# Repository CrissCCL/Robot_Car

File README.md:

# 🚗🤖 Assisted-Trajectory Robot Car

## 📖 Overview
This model robot car was developed and built to implement an assisted-trajectory (Drive by Wire) system. The system is controlled using a Teensy 4.0 microcontroller to enhance computational speed and stability.  

A gyroscope MPU6050 measures angular rate, while an H-bridge L298N drives the motors. The robot is operated via a Flysky FS-6X remote using a PPM/PWM modulated signal.

## 🧩 Hardware Notes — Pin Availability

The currently implemented PCB used in this robot car **does not expose Teensy 4.0 pins 12 and 13**, as the original board was designed for a specific application and limited I/O requirements.

As part of an ongoing hardware update, a **new pin expansion and routing strategy** is being developed.  
This updated PCB revision exposes **all relevant Teensy 4.0 pins**, including pins **12 and 13**, enabling greater flexibility and reuse across multiple projects.

This improvement aligns with the goal of creating **modular and reusable hardware blocks** that can be shared across multiple projects.

> 🔗 **NOTE:**  
> The updated pin expansion hardware is referenced in the **Related Repositories** section at the end of this document.

## 📂 Contents
- `/Hardware` → schematic, Gerbers.
- `/control_car` → C code for Teensy in the Arduino environment.
- `/control_car_bumpless_fix` → C code for Teensy in the Arduino environment, bumpless transfer bug fixed.

## 🌐 YouTube
📺 [My Playlist](https://youtube.com/playlist?list=PLy6JmHc8bVqIY5rbHkpyFbhlm4xQOCF1T&si=1QBgLZTLAjbxRnrU)

## ⚙️ System Description — Auto Robot (Assisted-Trajectory)
- **Controller:** Teensy 4.0 (high-speed MCU for improved stability and processing)  
- **Sensors:** Gyroscope (angular velocity) and supporting encoders/IMU as available  
- **Actuators:** Dual DC motors with H-bridge driver  
- **Control Strategy:** PI-assisted trajectory control (drive-by-wire)  
- **Sampling period:** **0.004 seconds (250 Hz)**  
- **Data transmission:** UART link to a **Raspberry Pi 4B** for logging and postprocessing  
- **Data logging:** Raspberry Pi saves incoming telemetry to `.csv` files for analysis  
- **Visualization:**  Offline monitoring and plotting via Matlab

## 🔄 Control Loop

### Controlled Variables
- **Yaw** → Angular velocity control (rotation rate)

## 📐 Digital PID Control

The PID controllers implemented in this project are **incremental (velocity form)** and use **trapezoidal integration** for the integral term.  
This ensures:
- Accurate discrete-time implementation suitable for microcontrollers.
- Consistency between simulation and embedded hardware behavior.
- Avoidance of integral windup when combined with actuator saturation or anti-windup mechanisms.

The UAV uses a discrete PI controller implemented on a Teensy microcontroller.  
The control law in the digital domain is expressed as:

$$
u(n) = u(n-1) + K_0 e(n) + K_1 e(n-1)
$$

Digital PI controller implemented for Yaw rate measured in Gyroscope,

$$
Gyro_{PWM}(n) = Gyro_{PWM}(n-1) + K_0 e(n) + K_1 e(n-1)
$$

### Parameters:
The parameters are adjusted for the angular rate,

$$
K_0 = K_p + \frac{K_p}{2T_i} T_s
$$

$$
K_1 = -K_p + \frac{K_p}{2T_i} T_s
$$

### Control Signal:

$$
motor_1=PWR_{PWM}+Gyro_{PWM}
$$
$$
motor_2=PWR_{PWM}-Gyro_{PWM}
$$

## :triangular_ruler: Connection Diagram

## 🧪 PI Control Test and ARX Model Comparison  

A test was performed using a **PI controller** applied to the assisted trajectory system of the robot car.  
The experimental results were compared against a **linear ARX model** identified from system data.  

### 🔹 General ARX Model Equation  

The ARX (Auto-Regressive with eXogenous input) model is defined as:  

$$
y(k) + a_1 y(k-1) + a_2 y(k-2) + \dots + a_{n_a} y(k-n_a) =
b_1 u(k-1) + b_2 u(k-2) + \dots + b_{n_b} u(k-n_b) + e(k)
$$  

Where:  
- $$y(k)$$: system output at sample $$k$$ 
- $$u(k)$$: input signal at sample $$k$$  
- $$( a_i, b_j)$$: ARX parameters  
- $$( n_a, n_b)$$: model orders  
- $$e(k) $$: disturbance/noise  

### 🔹 Results Overview  
- ✅ The PI controller improved **trajectory tracking** and reduced steady-state error.  
- 📉 The ARX model provided a good approximation of the system dynamics, with slight deviations due to unmodeled nonlinearities.  
- ⚖️ The comparison validates the feasibility of using simple parametric models (ARX) for **controller design and evaluation**.  

### 🔹 Experimental Plots  

## 🖼️ Render 3D PCB

## ⚡ Physical Prototype

<table>
  <tr>
    <td align="center">
      <br>
      <sub>Assembly device</sub>
    </td>
    <td align="center">
      <br>
      <sub>Complete setup</sub>
    </td>
  </tr>
</table>

## 🔗 Related Repositories

For additional tutorials and examples related to digital control simulations, visit:

- [Digital Control — Anti-Windup (Positional PI)](https://github.com/CrissCCL/Digital_ControlAntiWindup)
- [Digital Control Simulation — First Order System + Saturation](https://github.com/CrissCCL/Digital_ControlSim)
- [Digital Control Simulation — ARX Model + Saturation](https://github.com/CrissCCL/Digital_ControlSimARX)

An updated Teensy 4.0 pin expansion shield is available and can be reused across different projects:
- [Teensy 4.0 Pin Expansion Shield](https://github.com/CrissCCL/Teensy_SHIELD)

## 🤝 Support projects
 Support me on Patreon [https://www.patreon.com/c/CrissCCL](https://www.patreon.com/c/CrissCCL)

## 📜 License
MIT License

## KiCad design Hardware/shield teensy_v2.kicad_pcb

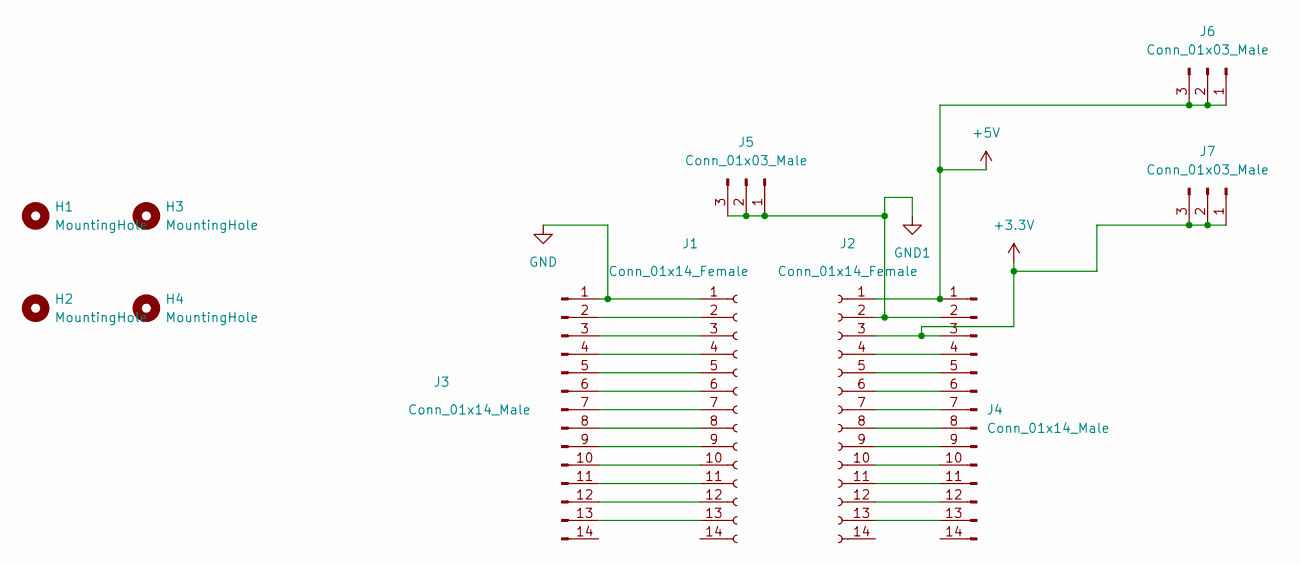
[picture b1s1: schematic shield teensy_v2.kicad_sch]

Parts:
H1, H2, H3, H4: MountingHole; MountingHole_3.2mm_M3_ISO7380_Pad
J1, J2: Conn_01x14_Female; PinSocket_1x14_P2.54mm_Vertical
J3, J4: Conn_01x14_Male; PinSocket_1x14_P2.54mm_Vertical
J5, J6, J7: Conn_01x03_Male; PinSocket_1x03_P2.54mm_Vertical

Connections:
+3.3V: J2.3, J4.3, J7.1, J7.2, J7.3
+5V: J2.1, J4.1, J6.1, J6.2, J6.3
GND: J1.1, J3.1
GND1: J2.2, J4.2, J5.1, J5.2, J5.3
unnamed: J1.2, J3.2
unnamed: J1.3, J3.3
unnamed: J1.4, J3.4
unnamed: J1.5, J3.5
unnamed: J1.6, J3.6
unnamed: J1.7, J3.7
unnamed: J1.8, J3.8
unnamed: J1.9, J3.9
unnamed: J1.10, J3.10
unnamed: J1.11, J3.11
unnamed: J1.12, J3.12
unnamed: J1.13, J3.13
unnamed: J2.4, J4.4
unnamed: J2.5, J4.5
unnamed: J2.6, J4.6
unnamed: J2.7, J4.7
unnamed: J2.8, J4.8
unnamed: J2.9, J4.9
unnamed: J2.10, J4.10
unnamed: J2.11, J4.11
unnamed: J2.12, J4.12
unnamed: J2.13, J4.13

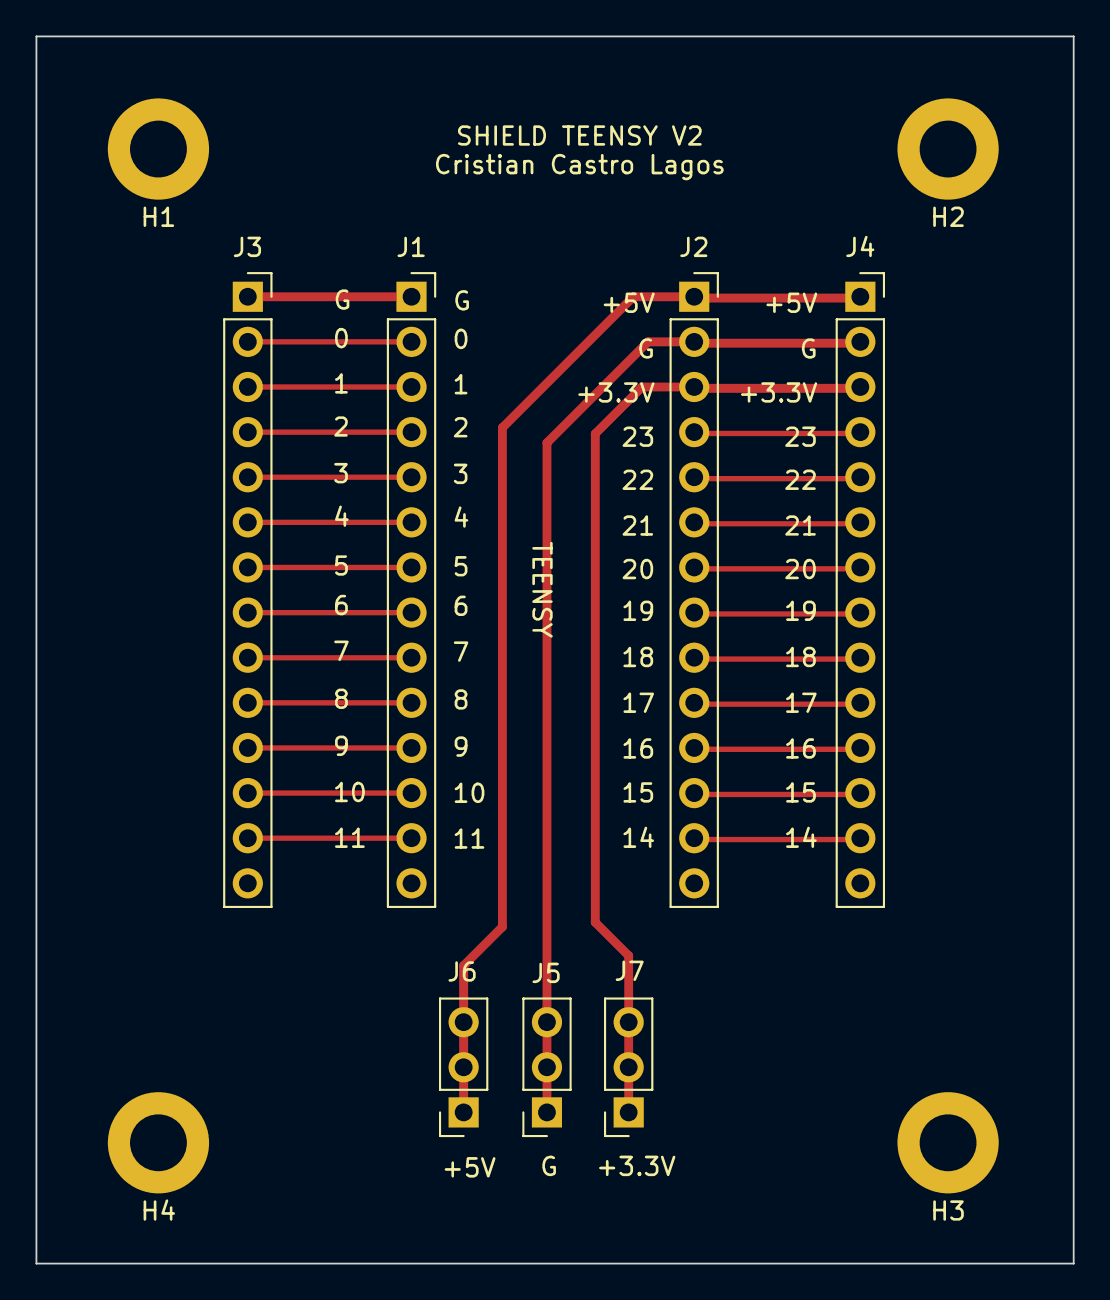
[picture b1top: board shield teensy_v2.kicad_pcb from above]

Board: 2 copper layers, 58.4 x 69.1 mm, 11 parts (0 on the bottom side), 26 nets.

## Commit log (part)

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2025-09-26 Rename conexiones.PNG to conexiones.png
2025-10-24 Fix image tag in README for PCB render
2025-12-18 Revise hardware update notice in README
    Updated hardware notice and related repositories reference.
2026-02-07 Update LICENSE
